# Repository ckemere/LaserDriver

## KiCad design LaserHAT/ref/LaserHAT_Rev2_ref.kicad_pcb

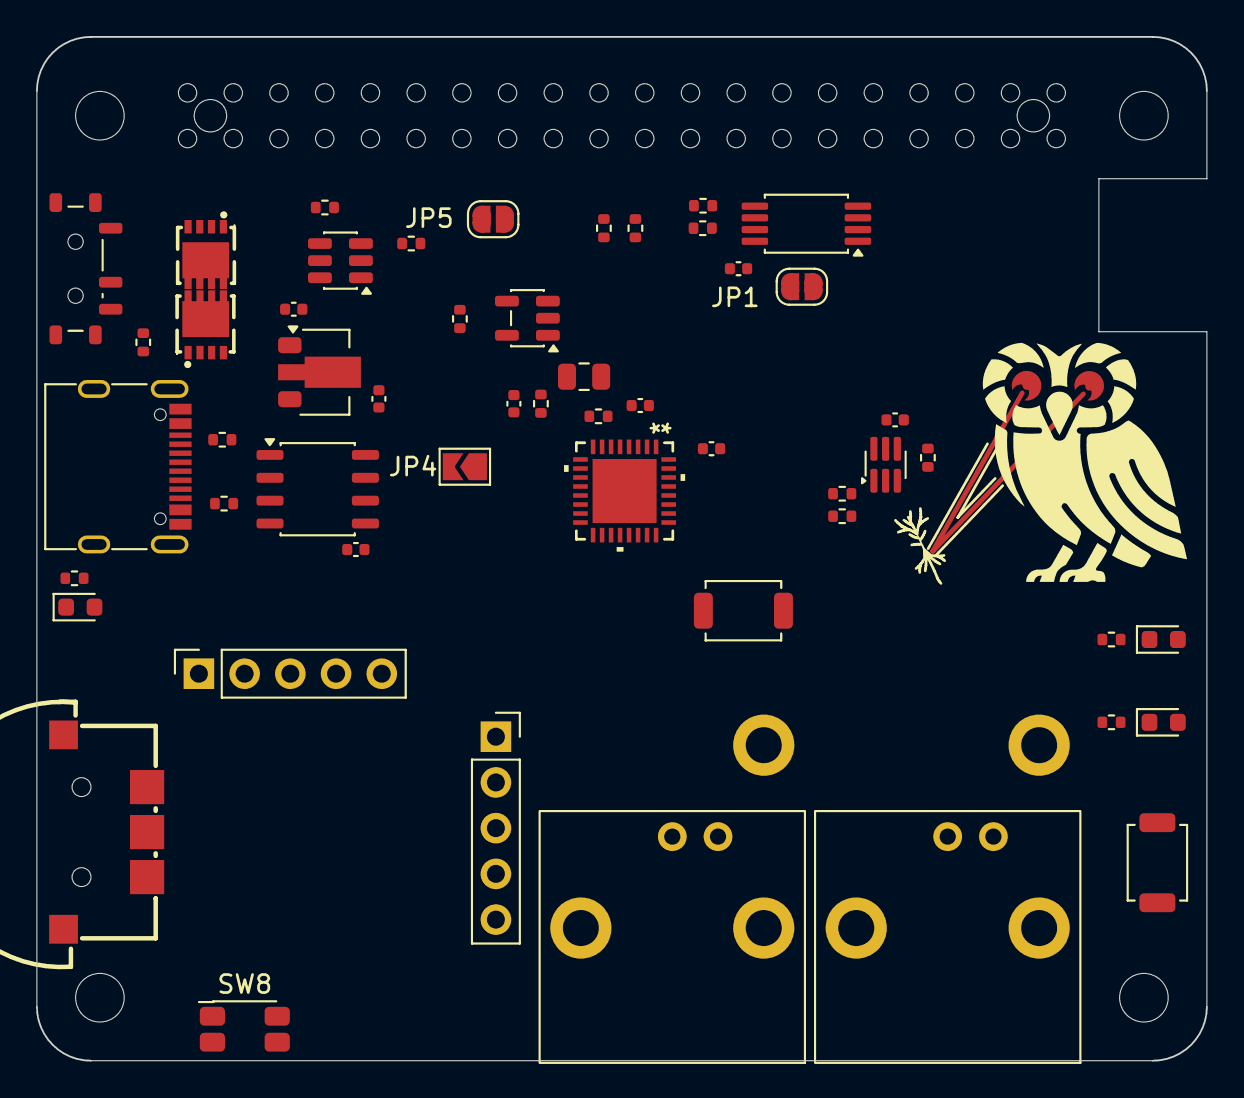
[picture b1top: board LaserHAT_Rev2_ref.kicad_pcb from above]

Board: 2 copper layers, 65.0 x 56.9 mm, 58 parts (1 on the bottom side), 53 nets, no tracks yet.

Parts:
C1, C6, C12, C15, C16: 100nF; C_0402_1005Metric
C2: 10uF; C_0805_2012Metric
C3: 10nF; C_0402_1005Metric
C4: 0.47uF; C_0402_1005Metric
C13: 1uF Ceramic; C_0402_1005Metric
D5: KT-0603W; D_0603_1608Metric
D7, D9: KT-0603R; D_0603_1608Metric
G1: OwlLogo; OwlLogo_Laser_14mm
J1: GPIO; Samtec_HLE-120-02-xxx-DV-BE-LC_2x20_P2.54mm_Horizontal
J5: GT-USB-7010ASV; USB_C_Receptacle_G-Switch_GT-USB-7010ASV
J6: BNC TRIGGER IN; BNC_Amphenol_031-5540_031-5539_Dual
J7: BNC STIM OUT; BNC_Amphenol_031-5540_031-5539_Dual
J8: DB_POWER_TIMING; PinSocket_1x05_P2.54mm_Vertical
J9: DB_ANALOG; PinSocket_1x05_P2.54mm_Vertical
JP1: ID_WP; SolderJumper-2_P1.3mm_Open_RoundedPad1.0x1.5mm
JP4: RTS_NRST; SolderJumper-2_P1.3mm_Open_TrianglePad1.0x1.5mm
JP5: STANDALONE_3V3; SolderJumper-2_P1.3mm_Open_RoundedPad1.0x1.5mm
MH1, MH2, MH3, MH4: MountingHole_2.7mm_M2.5
Q3, Q5: AP30P30Q; PDFN3333-8_PMOS_GSD
Q4: DMMT5401; SOT-23-6
R1, R2: 3.9k; R_0402_1005Metric
R3, R21: 47k; R_0402_1005Metric
R4: 100k 0.1%; R_0402_1005Metric
R7, R22: 10k; R_0402_1005Metric
R8, R10: 5.1k; R_0402_1005Metric
R13, R15, R18: 2k; R_0402_1005Metric
R19, R20: 4.7k; R_0402_1005Metric
R23: 1k; R_0402_1005Metric
R24, R26: 100k; R_0402_1005Metric
R25: 33; R_0402_1005Metric
SW6, SW9: TS-1088-AR02016; SW_SPST_TS-1088-xR020
SW7: BL-DT; SW-SMD_BL-DT
SW8: EVQP7A01P; SW_SPST_EVQP7A
SW10: MSK12C02; SW_SPDT_Shouhan_MSK12C02
U1: M24C32-WDW6TP; TSSOP-8_4.4x3mm_P0.65mm
U4: MCP1700x-330xxMB; SOT-89-3
U5: AP2171W; SOT-23-5
U6: CH340N; JEITA_SOIC-8_3.9x4.9mm_P1.27mm
U7: MSPM0G3507SRHBR; VQFN32_RHB_TEX
U8: 74LVC2G17; SOT-363_SC-70-6

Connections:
+3V3: C6.1, C13.1, JP5.1 (A), R7.1, U4.3 (VO), U5.5 (IN), U6.5 (VCC), U6.8 (V3)
+5V: C12.1, D5.2 (A), J1.2, J1.4, J8.2, Q3.2 (S), Q4.5 (E2), U4.2 (VI)
/BNC + Daughterboard I/O/BNC_IN: J6.1 (In), R23.2
/BNC + Daughterboard I/O/BNC_OUT: J7.1 (In), R25.1
/BNC + Daughterboard I/O/BUF_IN: R23.1, R24.1, U8.1
/BNC + Daughterboard I/O/BUF_OUT: D9.2 (A), R25.2, U8.4
/BNC + Daughterboard I/O/STIM_LED_K: D9.1 (K), R18.1
/GPIO18/PCM.CLK: J1.12, R7.2, U5.4 (EN)
/GPIO23: C3.1, J1.16, JP4.1 (A), R3.2, U7.3 (NRST)
/GPIO24: J1.18, U7.24 (PA20/SWCLK)
/GPIO25: J1.22, U7.23 (PA19/SWDIO)
/ID_SCL: J1.28, R2.2, U1.6 (SCL)
/ID_SDA: J1.27, R1.2, U1.5 (SDA)
/MCU_UART_RX: U6.6 (TXD), U7.15 (PA11)
/MCU_UART_TX: U6.7 (RXD), U7.14 (PA10/CLK_OUT)
/MSPM0 Controller/BUTTON1: SW8.1, U7.25 (PA21/A1_7/VREF-)
/MSPM0 Controller/BUTTON2: SW7.C, U7.18 (PA14/CLK_OUT/A0_12)
/MSPM0 Controller/BUTTON3: SW7.D, U7.20 (PA16/A1_1/FCC_IN)
/MSPM0 Controller/BUTTON4: SW7.B, U7.17 (PA13)
/MSPM0 Controller/BUTTON5: SW9.1, U7.27 (PA23/VREF+)
/MSPM0 Controller/MSPM0_BSL_INVOKE: SW6.1, U7.22 (PA18/A1_3)
/USB-C UART/CH340_RTS: JP4.2 (B), U6.4 (~RTS)
/USB-C UART/IDEAL_B: Q4.1 (C1), Q4.2 (B1), Q4.3 (B2), R21.1
/USB-C UART/IDEAL_G: Q3.1 (G), Q4.4 (C2), R22.1
/USB-C UART/PWR_EN: Q5.1 (G), R26.2, SW10.2 (B)
/USB-C UART/VBUS: J5.A4 (VBUS), J5.A9 (VBUS), J5.B4 (VBUS), J5.B9 (VBUS), Q5.2 (S), R26.1
/USB-C UART/VBUS_SW: Q3.3 (D), Q4.6 (E1), Q5.3 (D)
DB_ADC_A: J9.4, U7.21 (PA17/A1_2)
DB_ADC_B: J9.5, U7.26 (PA22/CLK_OUT/A0_7)
DB_DAC: J9.3, U7.19 (PA15/A1_0/DAC_OUT)
DB_GPIO: J8.3, U7.10 (PA6/HFCLK_IN/HFXOUT)
DB_PWM_A: J8.5, U7.11 (PA7/CLK_OUT)
DB_PWM_B: J8.4, U7.16 (PA12/FCC_IN)
GND: C1.2, C2.2, C3.2, C4.2, C6.2, C12.2, C13.2, C15.2, C16.2, G1.1 (GND), J1.6, J1.9, J1.14, J1.20, J1.25, J1.30, J1.34, J1.39, J5.A1 (GND), J5.A12 (GND), J5.B1 (GND), J5.B12 (GND), J5.S1 (SHIELD), J6.2 (Ext), J7.2 (Ext), J8.1, J9.1, R4.2, R8.2, R10.2, R13.2, R15.2, R18.2, R21.2, R22.2, R24.2, SW7.A, SW8.2, SW9.2, SW10.1 (A), U1.4 (GND), U4.1 (GND), U5.2 (GND), U6.3 (GND), U7.5 (VSS), U7.33 (EPAD), U8.2 (GND)
I2C_SCL: J1.5, R20.2, U7.2 (PA1)
I2C_SDA: J1.3, R19.2, U7.1 (PA0/FCC_IN)
LED_MCU: D7.2 (A), U7.28 (PA24/A0_3)
MCU_STIM_IN: U7.30 (PA26/A0_1), U8.6
MCU_STIM_OUT: U7.29 (PA25/A0_2/OPA0_IN1+), U8.3
MSPM0_3V3: C1.1, C2.1, C16.1, J9.2, R3.1, SW6.2, U5.1 (OUT), U7.4 (VDD), U8.5 (VCC)
unnamed: D5.1 (K), R13.1
unnamed: D7.1 (K), R15.1
unnamed: J5.A5 (CC1), R8.1
unnamed: J5.B5 (CC2), R10.1
unnamed: JP1.1 (A), U1.7 (WP)
unnamed: J5.A6 (D+), J5.B6 (D+), U6.1 (UD+)
unnamed: J5.A7 (D-), J5.B7 (D-), U6.2 (UD-)
PI_RXD: J1.10, U7.12 (PA8)
PI_TRIGGER: J1.37, U7.31 (PA27/RTC_OUT/A0_0)
PI_TXD: J1.8, U7.13 (PA9/RTC_OUT/CLK_OUT)
ROSC: R4.1, U7.6 (PA2/ROSC)
RPi +3V3: C15.1, J1.1, J1.17, JP1.2 (B), JP5.2 (B), R1.1, R2.1, R19.1, R20.1, U1.8 (VCC)
VCORE: C4.1, U7.32 (VCORE)

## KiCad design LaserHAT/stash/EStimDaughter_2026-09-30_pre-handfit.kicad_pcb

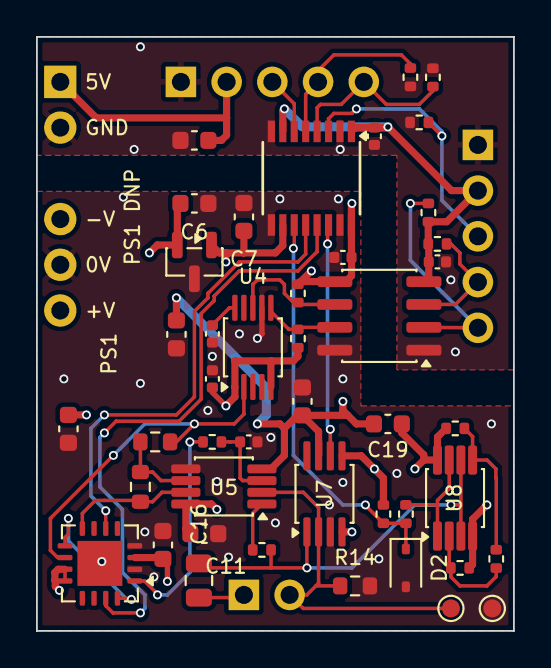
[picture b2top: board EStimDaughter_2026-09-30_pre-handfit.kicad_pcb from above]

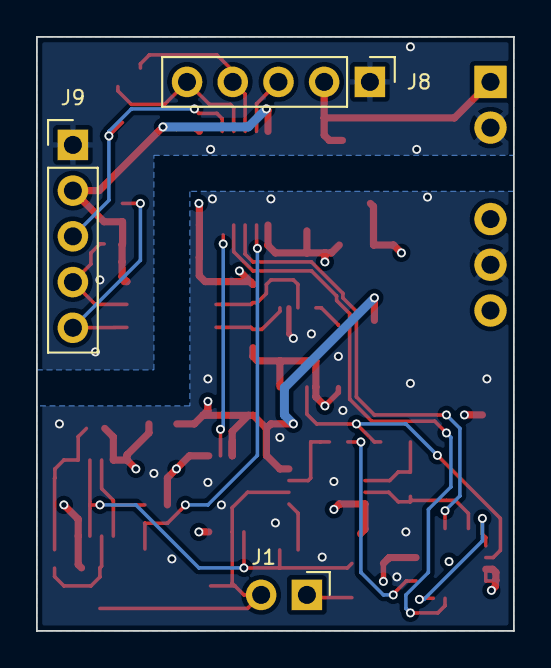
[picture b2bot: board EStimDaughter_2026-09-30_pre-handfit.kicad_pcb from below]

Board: 4 copper layers, 26.5 x 33.0 mm, 48 parts (3 on the bottom side), 33 nets.

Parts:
C1, C2, C9, C10, C17: 100n; C_0402_1005Metric
C3: 4.7u; C_0603_1608Metric
C5, C6, C7: 1u 50V; C_0603_1608Metric
C11, C12, C13, C14, C19: 100n; C_0603_1608Metric
C15: 100p; C_0402_1005Metric
C16: 1u 50V; C_0805_2012Metric
D2: BAT54WS; D_SOD-323
J1: ELECTRODE E1/E2; PinHeader_1x02_P2.54mm_Horizontal
J8: J8 power/timing (underside); PinHeader_1x05_P2.54mm_Vertical
J9: J9 I2C/release (underside); PinHeader_1x05_P2.54mm_Vertical
PS1: A0515S-1WR3; DCDC_SIP6_A0515S
R1, R2, R3: 100k; R_0402_1005Metric
R7, R8, R9, R15, R19: 4.7k; R_0402_1005Metric
R10, R11: 10.0k 0.1%; R_0603_1608Metric
R12: 1k; R_0402_1005Metric
R13: 47; R_0402_1005Metric
R14: 2.49k 0.1%; R_0603_1608Metric
R23, R25, R26: 10k; R_0402_1005Metric
R24: 215k; R_0402_1005Metric
TP1: ISENSE; TestPoint_Pad_D1.0mm
TP2: GND_ISO; TestPoint_Pad_D1.0mm
U1: ISO7741FDBQR; SSOP-16_3.9x4.9mm_P0.635mm
U2: TLV76050DBZR; SOT-23
U4: DAC60501ZDGSR; VSSOP-10_3x3mm_P0.5mm
U5: OPA2192IDGKR; VSSOP-8_3x3mm_P0.65mm
U6: ADG1436YCPZ; QFN-16-1EP_4x4mm_P0.65mm_EP2.5x2.5mm
U7: DG419BDQ; MSOP-8_3x3mm_P0.65mm
U8: TLV1702AIDGKR; VSSOP-8_3x3mm_P0.65mm
U9: ISO1640BDR; SOIC-8_3.9x4.9mm_P1.27mm

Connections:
+3V3_H: C1.1, C17.1, J9.2, R7.1, R8.1, U1.1 (VCC1), U1.7 (EN1), U9.4 (VCC1)
+5V_H: C3.1, J8.2, PS1.1 (+VIN)
+5V_ISO: C2.1, C7.1, C10.1, R9.1, R15.1, R19.1, U1.10 (EN2), U1.16 (VCC2), U2.1 (OUT), U4.1 (VDD), U4.5 (SPI2C), U7.5 (VL), U9.5 (VCC2)
+V_STIM: C6.1, C11.1, C13.1, C19.1, PS1.6 (+VO), R23.1, U2.2 (IN), U5.8 (V+), U6.11 (VDD), U6.12 (EN), U7.4 (V+), U8.8 (V+)
-V_STIM: C5.2, C12.2, C14.2, C19.2, PS1.4 (-VO), R25.2, U5.4 (V-), U6.3 (VSS), U6.17 (EP), U7.7 (V-), U8.4 (V-)
/CATH_H: J8.4, R2.1, U1.5 (INC)
/EN_H: J8.5, R1.1, U1.4 (INB)
/FAULT_H: J8.3, U1.6 (OUTD)
/FAULT_OC: R26.1, U8.1, U8.7
/RELEASE_H: J9.3, R3.1, U1.3 (INA)
/SCL_H: J9.5, R8.2, U9.2 (SDA1)
/SDA_H: J9.4, R7.2, U9.3 (SCL1)
/SW_P: U6.9 (D2), U6.16 (S1A)
/VSET_N: R11.2, U5.7, U6.8 (S2A)
/VSET_P: R10.1, U4.2 (VOUT), U6.10 (S2B)
CATH: U1.12 (OUTC), U6.6 (IN2)
E1: C16.1, R13.2, U7.1 (D), U8.3 (+), U8.6 (-)
EN: U1.13 (OUTB), U6.15 (IN1)
FAULT_n: D2.1 (K), R19.2, R26.2, U1.11 (IND)
GND_H: C1.2, C3.2, C17.2, J8.1, J9.1, PS1.2 (-VIN), R1.2, R2.2, R3.2, U1.2 (GND1), U1.8 (GND1), U9.1 (GND1)
GND_ISO: C2.2, C5.1, C6.2, C7.2, C9.2, C10.2, C11.2, C12.1, C13.2, C14.1, C15.2, D2.2 (A), PS1.5 (COM), R14.2, TP2.1, U1.9 (GND2), U1.15 (GND2), U2.3 (GND), U4.4 (AGND), U4.7 (A0), U5.5 (+), U6.2 (S1B), U6.4 (GND), U7.3 (GND), U9.8 (GND2)
ISENSE: J1.2, R14.1, TP1.1, U5.2 (-), U7.2 (S1)
unnamed: C16.2, J1.1
unnamed: R13.1, U5.1
unnamed: C9.1, U4.10 (VREFIO)
unnamed: C15.1, R12.2, U5.3 (+)
unnamed: R10.2, R11.1, U5.6 (-)
unnamed: R24.2, R25.1, U8.2 (-)
unnamed: R23.2, R24.1, U8.5 (+)
RELEASE: U1.14 (OUTA), U7.6 (IN)
SCL: R15.2, U4.6 (SCL), U9.7 (SDA2)
SDA: R9.2, U4.8 (SDA), U9.6 (SCL2)
V_IN: R12.1, U6.1 (D1)

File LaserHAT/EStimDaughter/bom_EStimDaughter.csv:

Ref,Value,Footprint,LCSC,Note
J8,J8 power/timing (underside),PinHeader_1x05_P2.54mm_Vertical,,
J9,J9 I2C/release (underside),PinHeader_1x05_P2.54mm_Vertical,,
R1,100k,R_0402_1005Metric,C25741,
R2,100k,R_0402_1005Metric,C25741,
R3,100k,R_0402_1005Metric,C25741,
R7,4.7k,R_0402_1005Metric,C25900,
R8,4.7k,R_0402_1005Metric,C25900,
U1,ISO7741FDBQR,SSOP-16_3.9x4.9mm_P0.635mm,C2872241,
C1,100n,C_0402_1005Metric,C1525,
C2,100n,C_0402_1005Metric,C1525,
U9,ISO1640BDR,SOIC-8_3.9x4.9mm_P1.27mm,C5122339,
C17,100n,C_0402_1005Metric,C1525,
R9,4.7k,R_0402_1005Metric,C25900,
R15,4.7k,R_0402_1005Metric,C25900,
C3,4.7u,C_0603_1608Metric,C69335,
C5,1u 50V,C_0603_1608Metric,C559769,
U2,TLV76050DBZR,SOT-23,C2867465,
C6,1u 50V,C_0603_1608Metric,C559769,
C7,1u 50V,C_0603_1608Metric,C559769,
U4,DAC60501ZDGSR,VSSOP-10_3x3mm_P0.5mm,C1852027,
C9,100n,C_0402_1005Metric,C1525,
C10,100n,C_0402_1005Metric,C1525,
U5,OPA2192IDGKR,VSSOP-8_3x3mm_P0.65mm,C2876419,
C11,100n,C_0603_1608Metric,C14663,
C12,100n,C_0603_1608Metric,C14663,
R10,10.0k 0.1%,R_0603_1608Metric,C95204,
R11,10.0k 0.1%,R_0603_1608Metric,C95204,
U6,ADG1436YCPZ,QFN-16-1EP_4x4mm_P0.65mm_EP2.5x2.5mm,C655227,
C13,100n,C_0603_1608Metric,C14663,
C14,100n,C_0603_1608Metric,C14663,
R12,1k,R_0402_1005Metric,C11702,
C15,100p,C_0402_1005Metric,C1546,
R13,47,R_0402_1005Metric,C137973,
R14,2.49k 0.1%,R_0603_1608Metric,C861299,
C16,1u 50V,C_0805_2012Metric,C726584,
J1,ELECTRODE E1/E2,PinHeader_1x02_P2.54mm_Horizontal,,
U7,DG419BDQ,MSOP-8_3x3mm_P0.65mm,C2673354,
R19,4.7k,R_0402_1005Metric,C25900,
R23,10k,R_0402_1005Metric,C25744,
R24,215k,R_0402_1005Metric,C185443,
R25,10k,R_0402_1005Metric,C25744,
U8,TLV1702AIDGKR,VSSOP-8_3x3mm_P0.65mm,C2870937,
R26,10k,R_0402_1005Metric,C25744,
D2,BAT54WS,D_SOD-323,C124205,
C19,100n,C_0603_1608Metric,C14663,

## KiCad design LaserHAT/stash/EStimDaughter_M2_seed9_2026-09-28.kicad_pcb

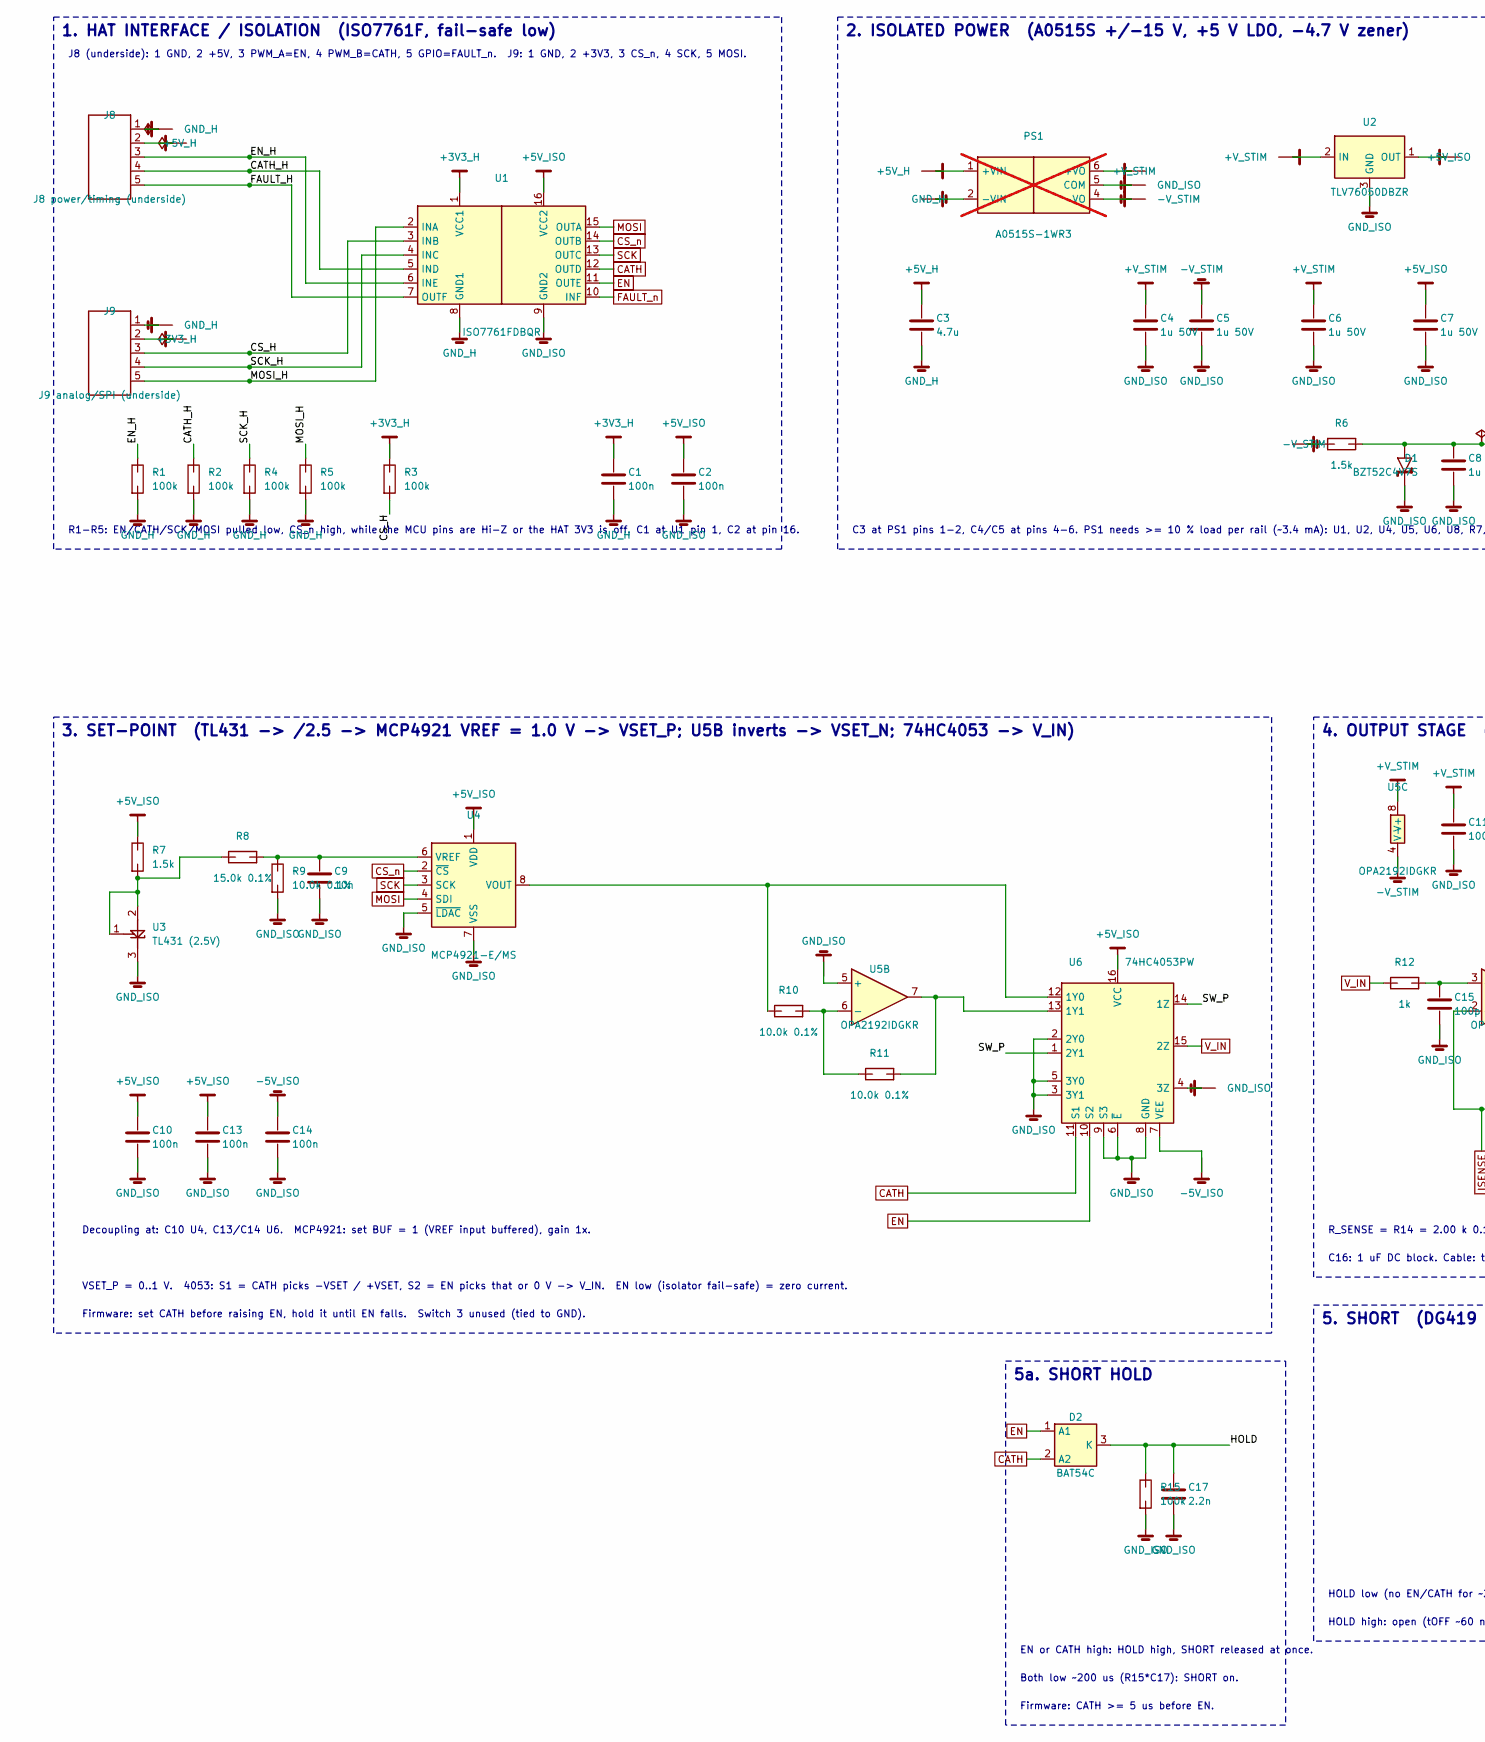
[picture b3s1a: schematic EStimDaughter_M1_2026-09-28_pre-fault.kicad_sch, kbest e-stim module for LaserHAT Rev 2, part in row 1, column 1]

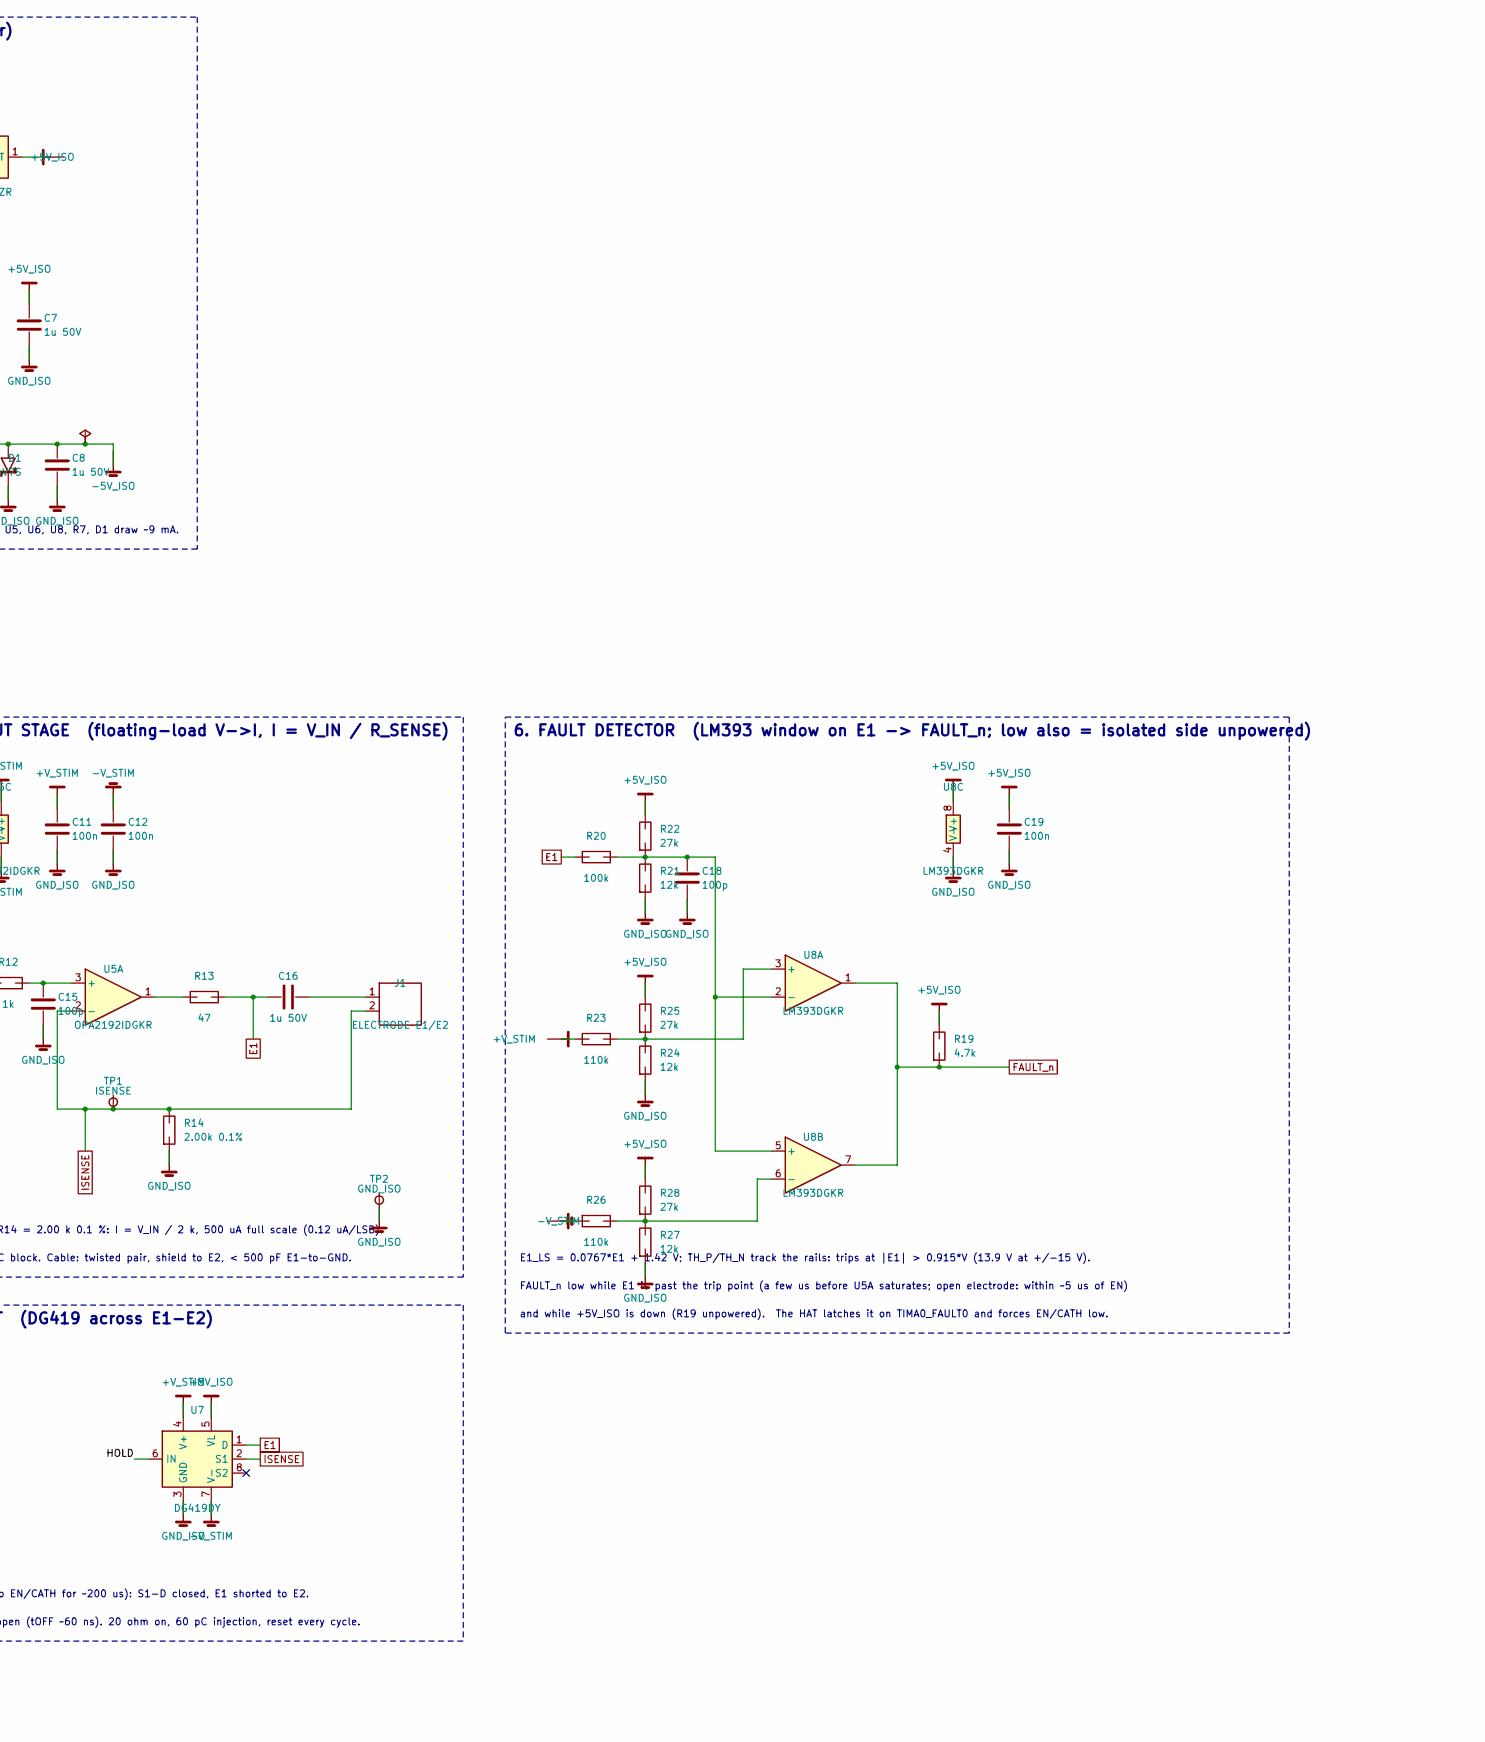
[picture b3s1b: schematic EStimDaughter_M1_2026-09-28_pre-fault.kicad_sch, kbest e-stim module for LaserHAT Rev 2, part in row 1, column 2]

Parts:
C1, C2, C10, C13, C14, C19: 100n; C_0402_1005Metric; LCSC C1525
C3: 4.7u; C_0603_1608Metric; LCSC C69335
C4, C5, C6, C7, C8: 1u 50V; C_0603_1608Metric; LCSC C559769
C9: 10n; C_0402_1005Metric; LCSC C15195
C11, C12: 100n; C_0603_1608Metric; LCSC C14663
C15, C18: 100p; C_0402_1005Metric; LCSC C1546
C16: 1u 50V; C_0805_2012Metric; LCSC C726584
C17: 2.2n; C_0402_1005Metric; LCSC C106861
D1: BZT52C4V7S; D_SOD-323; LCSC C19077439
D2: BAT54C; SOT-23; LCSC C37704
J1: ELECTRODE E1/E2; PinHeader_1x02_P2.54mm_Horizontal
J8: J8 power/timing (underside); PinHeader_1x05_P2.54mm_Vertical
J9: J9 analog/SPI (underside); PinHeader_1x05_P2.54mm_Vertical
PS1: A0515S-1WR3; DCDC_SIP6_A0515S; not fitted
R1, R2, R3, R4, R5, R15, R20: 100k; R_0402_1005Metric; LCSC C25741
R6, R7: 1.5k; R_0603_1608Metric; LCSC C22843
R8: 15.0k 0.1%; R_0603_1608Metric; LCSC C326733
R9, R10, R11: 10.0k 0.1%; R_0603_1608Metric; LCSC C95204
R12: 1k; R_0402_1005Metric; LCSC C11702
R13: 47; R_0402_1005Metric; LCSC C137973
R14: 2.00k 0.1%; R_0603_1608Metric; LCSC C328425
R19: 4.7k; R_0402_1005Metric; LCSC C25900
R21, R24, R27: 12k; R_0402_1005Metric; LCSC C25752
R22, R25, R28: 27k; R_0402_1005Metric; LCSC C22369538
R23, R26: 110k; R_0402_1005Metric; LCSC C2909311
TP1: ISENSE; TestPoint_Pad_D1.0mm
TP2: GND_ISO; TestPoint_Pad_D1.0mm
U1: ISO7761FDBQR; SSOP-16_3.9x4.9mm_P0.635mm; LCSC C2877505
U2: TLV76050DBZR; SOT-23; LCSC C2867465
U3: TL431 (2.5V); SOT-23; LCSC C181103
U4: MCP4921-E/MS; MSOP-8_3x3mm_P0.65mm; LCSC C185506
U5: OPA2192IDGKR; VSSOP-8_3x3mm_P0.65mm; LCSC C2876419
U6: 74HC4053PW; TSSOP-16_4.4x5mm_P0.65mm; LCSC C5648
U7: DG419DY; SOIC-8_3.9x4.9mm_P1.27mm; LCSC C6581
U8: LM393DGKR; VSSOP-8_3x3mm_P0.65mm; LCSC C34440

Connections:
+3V3_H: C1.1, J9.2, R3.1, U1.1 (VCC1)
+5V_H: C3.1, J8.2, PS1.1 (+VIN)
+5V_ISO: C2.1, C7.1, C10.1, C13.1, C19.1, R7.1, R19.1, R22.1, R25.1, R28.1, U1.16 (VCC2), U2.1 (OUT), U4.1 (VDD), U6.16 (VCC), U7.5 (VL), U8.8 (V+)
+V_STIM: C4.1, C6.1, C11.1, PS1.6 (+VO), R23.1, U2.2 (IN), U5.8 (V+), U7.4 (V+)
-5V_ISO: C8.2, C14.2, D1.2 (A), R6.1, U6.7 (VEE)
-V_STIM: C5.2, C12.2, PS1.4 (-VO), R6.2, R26.2, U5.4 (V-), U7.7 (V-)
CATH: D2.2 (A2), U1.12 (OUTD), U6.11 (S1)
CATH_H: J8.4, R2.1, U1.5 (IND)
CS_H: J9.3, R3.2, U1.3 (INB)
CS_n: U1.14 (OUTB), U4.2 (~CS)
E1: C16.1, R13.2, R20.1, U7.1 (D)
EN: D2.1 (A1), U1.11 (OUTE), U6.10 (S2)
EN_H: J8.3, R1.1, U1.6 (INE)
FAULT_H: J8.5, U1.7 (OUTF)
FAULT_n: R19.2, U1.10 (INF), U8.1, U8.7
GND_H: C1.2, C3.2, J8.1, J9.1, PS1.2 (-VIN), R1.2, R2.2, R4.2, R5.2, U1.8 (GND1)
GND_ISO: C2.2, C4.2, C5.1, C6.2, C7.2, C8.1, C9.2, C10.2, C11.2, C12.1, C13.2, C14.1, C15.2, C17.2, C18.2, C19.2, D1.1 (K), PS1.5 (COM), R9.2, R14.2, R15.2, R21.2, R24.2, R27.2, TP2.1, U1.9 (GND2), U2.3 (GND), U3.3 (A), U4.5 (~LDAC), U4.7 (VSS), U5.5 (+), U6.2 (2Y0), U6.3 (3Y1), U6.4 (3Z), U6.5 (3Y0), U6.6 (~E), U6.8 (GND), U6.9 (S3), U7.3 (GND), U8.4 (V-)
HOLD: C17.1, D2.3 (K), R15.1, U7.6 (IN)
ISENSE: J1.2, R14.1, TP1.1, U5.2 (-), U7.2 (S1)
MOSI: U1.15 (OUTA), U4.4 (SDI)
MOSI_H: J9.5, R5.1, U1.2 (INA)
unnamed: C16.2, J1.1
unnamed: R13.1, U5.1
unnamed: R7.2, R8.1, U3.1 (REF), U3.2 (K)
unnamed: R10.1, U4.8 (VOUT), U6.12 (1Y0)
unnamed: C9.1, R8.2, R9.1, U4.6 (VREF)
unnamed: C15.1, R12.2, U5.3 (+)
unnamed: R10.2, R11.1, U5.6 (-)
unnamed: R11.2, U5.7, U6.13 (1Y1)
unnamed: R23.2, R24.1, R25.2, U8.3 (+)
unnamed: C18.1, R20.2, R21.1, R22.2, U8.2 (-), U8.5 (+)
unnamed: R26.1, R27.1, R28.2, U8.6 (-)
SCK: U1.13 (OUTC), U4.3 (SCK)
SCK_H: J9.4, R4.1, U1.4 (INC)
SW_P: U6.1 (2Y1), U6.14 (1Z)
V_IN: R12.1, U6.15 (2Z)

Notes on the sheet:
1. HAT INTERFACE / ISOLATION (ISO7761F, fail-safe low)
R1-R5: EN/CATH/SCK/MOSI pulled low, CS_n high, while the MCU pins are Hi-Z or the HAT 3V3 is off. C1 at U1 pin 1, C2 at pin 16.
J8 (underside): 1 GND, 2 +5V, 3 PWM_A=EN, 4 PWM_B=CATH, 5 GPIO=FAULT_n. J9: 1 GND, 2 +3V3, 3 CS_n, 4 SCK, 5 MOSI.
2. ISOLATED POWER (A0515S +/-15 V, +5 V LDO, -4.7 V zener)
C3 at PS1 pins 1-2, C4/C5 at pins 4-6. PS1 needs >= 10 % load per rail (~3.4 mA): U1, U2, U4, U5, U6, U8, R7, D1 draw ~9 mA.
3. SET-POINT (TL431 -> /2.5 -> MCP4921 VREF = 1.0 V -> VSET_P; U5B inverts -> VSET_N; 74HC4053 -> V_IN)
Decoupling at: C10 U4, C13/C14 U6. MCP4921: set BUF = 1 (VREF input buffered), gain 1x.
VSET_P = 0..1 V. 4053: S1 = CATH picks -VSET / +VSET, S2 = EN picks that or 0 V -> V_IN. EN low (isolator fail-safe) = zero current.
Firmware: set CATH before raising EN, hold it until EN falls. Switch 3 unused (tied to GND).
4. OUTPUT STAGE (floating-load V->I, I = V_IN / R_SENSE)
R_SENSE = R14 = 2.00 k 0.1 %: I = V_IN / 2 k, 500 uA full scale (0.12 uA/LSB).
C16: 1 uF DC block. Cable: twisted pair, shield to E2, < 500 pF E1-to-GND.
5. SHORT (DG419 across E1-E2)
HOLD low (no EN/CATH for ~200 us): S1-D closed, E1 shorted to E2.
HOLD high: open (tOFF ~60 ns). 20 ohm on, 60 pC injection, reset every cycle.
6. FAULT DETECTOR (LM393 window on E1 -> FAULT_n; low also = isolated side unpowered)
E1_LS = 0.0767*E1 + 1.42 V; TH_P/TH_N track the rails: trips at |E1| > 0.915*V (13.9 V at +/-15 V).
FAULT_n low while E1 is past the trip point (a few us before U5A saturates; open electrode: within ~5 us of EN)
and while +5V_ISO is down (R19 unpowered). The HAT latches it on TIMA0_FAULT0 and forces EN/CATH low.
5a. SHORT HOLD
EN or CATH high: HOLD high, SHORT released at once.
Both low ~200 us (R15*C17): SHORT on.
Firmware: CATH >= 5 us before EN.

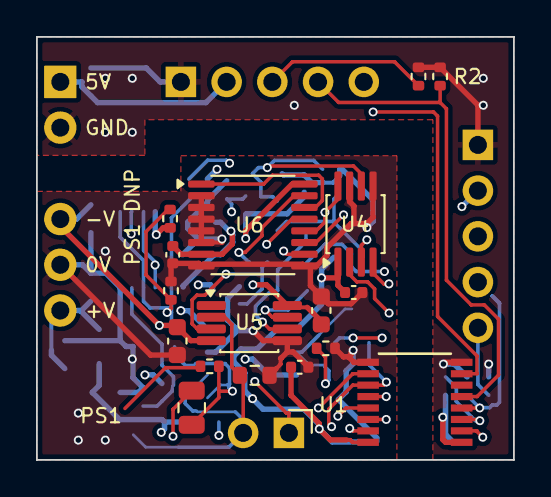
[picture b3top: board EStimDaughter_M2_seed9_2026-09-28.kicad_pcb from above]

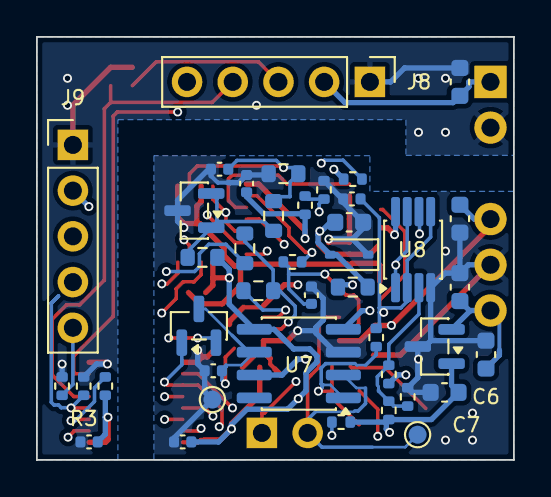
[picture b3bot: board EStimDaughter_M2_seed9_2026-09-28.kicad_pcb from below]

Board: 4 copper layers, 26.5 x 23.5 mm, 60 parts (41 on the bottom side), 36 nets.

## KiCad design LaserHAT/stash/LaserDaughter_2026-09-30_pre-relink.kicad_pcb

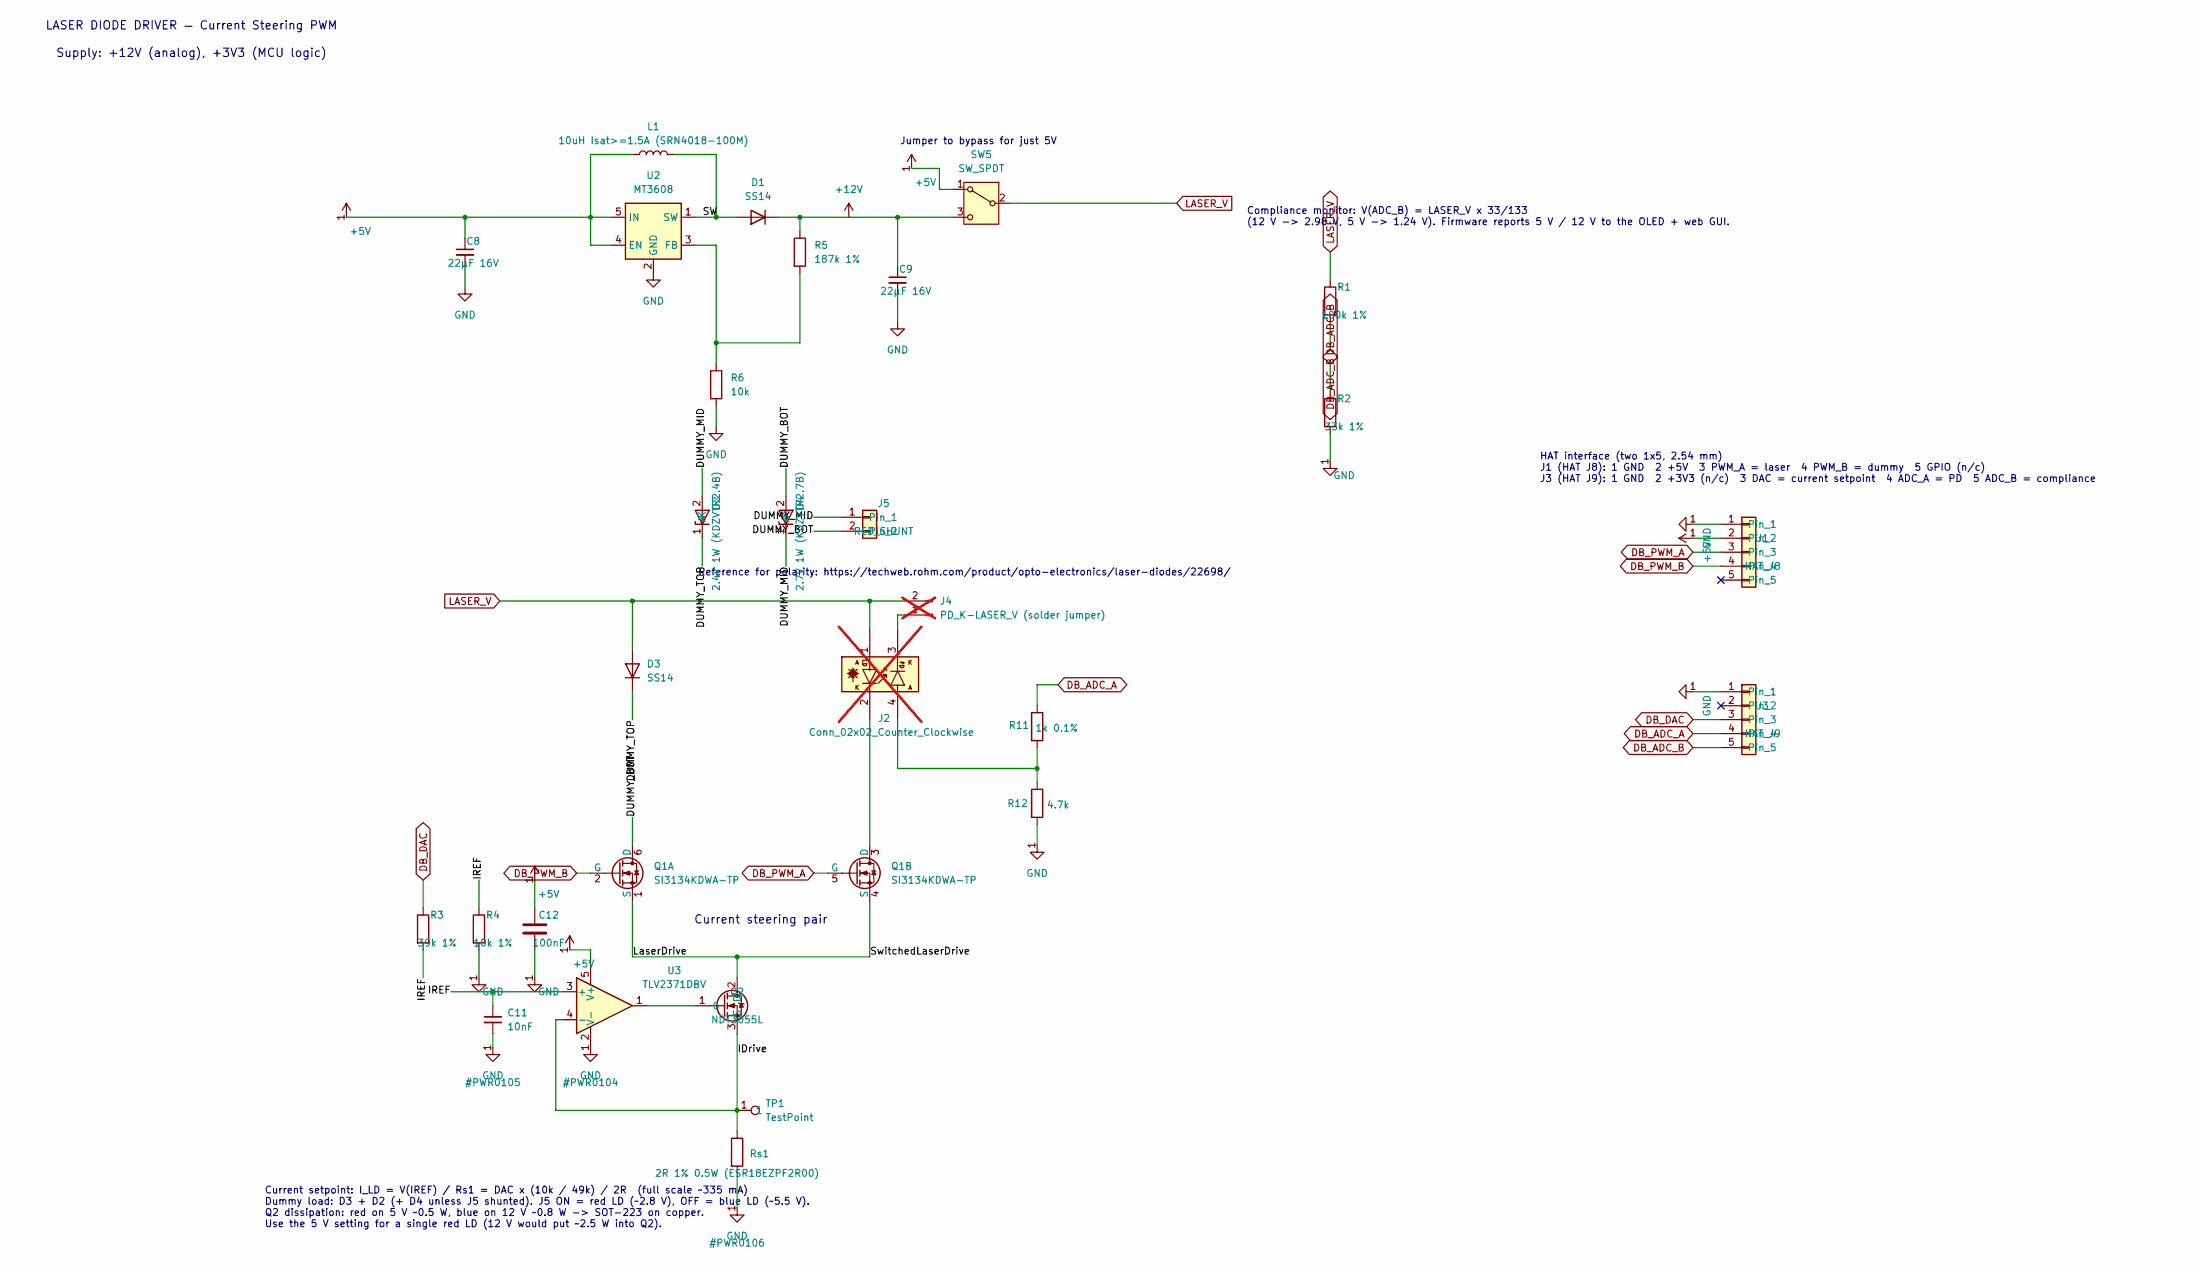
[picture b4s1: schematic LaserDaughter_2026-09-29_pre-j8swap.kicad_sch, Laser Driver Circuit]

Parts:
C8, C9: 22µF 16V; C_1206_3216Metric; LCSC Part # C12891
C11: 10nF; C_0402_1005Metric; LCSC Part # C15195
C12: 100nF; C_0402_1005Metric
D1: SS14; D_SOD-123F; LCSC Part # C894423
D2: 2.4V 1W (KDZVTR2.4B); D_SOD-123F
D3: SS14; D_SOD-123F; LCSC Part # C119617
D4: 2.7V 1W (KDZVTR2.7B); D_SOD-123F
J1: HAT_J8; PinHeader_1x05_P2.54mm_Vertical
J2: Conn_02x02_Counter_Clockwise; PinHeader_2x02_P2.54mm_Vertical; not fitted
J3: HAT_J9; PinHeader_1x05_P2.54mm_Vertical
J4: PD_K-LASER_V (solder jumper); SolderJumper-2_P1.3mm_Open_RoundedPad1.0x1.5mm; not fitted
J5: RED_SHUNT; PinHeader_1x02_P2.00mm_Vertical
L1: 10uH Isat>=1.5A (SRN4018-100M); L_Bourns-SRN4018; LCSC Part # C7427158
Q1: SI3134KDWA-TP; SOT-363_SC-70-6; LCSC Part # C3290118
Q2: NDT3055L; SOT-223-3_TabPin2
R1: 100k 1%; R_0402_1005Metric
R2: 33k 1%; R_0402_1005Metric
R3: 39k 1%; R_0402_1005Metric
R4: 10k 1%; R_0402_1005Metric
R5: 187k 1%; R_0402_1005Metric; LCSC Part # C844101
R6: 10k; R_0402_1005Metric; LCSC Part # C25744
R11: 1k 0.1%; R_0402_1005Metric; LCSC Part # C843869
R12: 4.7k; R_0402_1005Metric; LCSC Part # C25900
Rs1: 2R 1% 0.5W (ESR18EZPF2R00); R_1206_3216Metric; LCSC Part # C42460620
SW5: SW_SPDT; SW_SPDT_PCM12; LCSC Part # C221841
TP1: TestPoint; TestPoint_Pad_D1.5mm
U2: MT3608; SOT-23-6; LCSC Part # C84817
U3: TLV2371DBV; SOT-23-5; LCSC Part # C55940

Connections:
+5V: C8.1, C12.1, J1.2, L1.1, SW5.1 (A), U2.4 (EN), U2.5 (IN), U3.5 (IN)
+12V: C9.1, D1.1 (K), R5.1, SW5.3 (C)
/DUMMY_BOT: D4.2 (A), J5.2, Q1.6 (D)
/DUMMY_MID: D2.2 (A), D4.1 (K), J5.1
/DUMMY_TOP: D2.1 (K), D3.1 (K)
/IDrive: Q2.3 (S), Rs1.1, TP1.1, U3.4 (EN)
/IREF: C11.1, R3.2, R4.1, U3.3 (~FLG)
/LaserDrive: Q1.1 (S), Q1.4 (S), Q2.2 (D)
/SW: D1.2 (A), L1.2, U2.1 (SW)
DB_ADC_A: J3.4, R11.1
DB_ADC_B: J3.5, R1.2, R2.1
DB_DAC: J3.3, R3.1
DB_PWM_A: J1.3, J1.5, Q1.5 (G)
DB_PWM_B: J1.4, Q1.2 (G)
GND: C8.2, C9.2, C11.2, C12.2, J1.1, J3.1, R2.2, R4.2, R6.2, R12.2, Rs1.2, U2.2 (GND), U3.2 (GND)
LASER_V: D3.2 (A), J2.1 (LD_Anode), J4.2 (B), R1.1, SW5.2 (B)
unnamed: J2.2 (LD_Cathode), Q1.3 (D)
unnamed: J2.4 (PD_Anode), R11.2, R12.1
unnamed: J2.3 (PD_Cathode), J4.1 (A)
unnamed: Q2.1 (G), U3.1 (OUT)
unnamed: R5.2, R6.1, U2.3 (FB)

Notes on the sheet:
Supply: +12V (analog), +3V3 (MCU logic)
Current steering pair
LASER DIODE DRIVER — Current Steering PWM
Reference for polarity: https://techweb.rohm.com/product/opto-electronics/laser-diodes/22698/
Jumper to bypass for just 5V
Current setpoint: I_LD = V(IREF) / Rs1 = DAC x (10k / 49k) / 2R (full scale ~335 mA) Dummy load: D3 + D2 (+ D4 unless J5 shunted). J5 ON = red LD (~2.8 V), OFF = blue LD (~5.5 V). Q2 dissipation: red on 5 V ~0.5 W, blue on 12 V ~0.8 W -> SOT-223 on copper. Use the 5 V setting for a single red LD (1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
Compliance monitor: V(ADC_B) = LASER_V x 33/133 (12 V -> 2.98 V, 5 V -> 1.24 V). Firmware reports 5 V / 12 V to the OLED + web GUI.
HAT interface (two 1x5, 2.54 mm) J1 (HAT J8): 1 GND 2 +5V 3 PWM_A = laser 4 PWM_B = dummy 5 GPIO (n/c) J3 (HAT J9): 1 GND 2 +3V3 (n/c) 3 DAC = current setpoint 4 ADC_A = PD 5 ADC_B = compliance

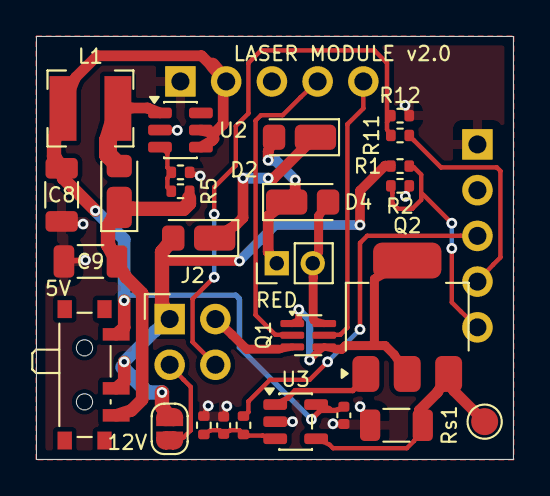
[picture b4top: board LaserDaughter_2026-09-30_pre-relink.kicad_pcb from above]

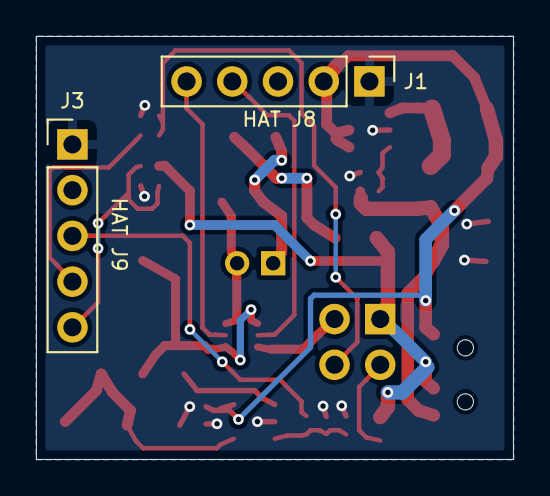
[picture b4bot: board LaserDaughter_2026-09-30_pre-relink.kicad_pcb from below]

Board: 2 copper layers, 26.5 x 23.5 mm, 29 parts (2 on the bottom side), 21 nets.
